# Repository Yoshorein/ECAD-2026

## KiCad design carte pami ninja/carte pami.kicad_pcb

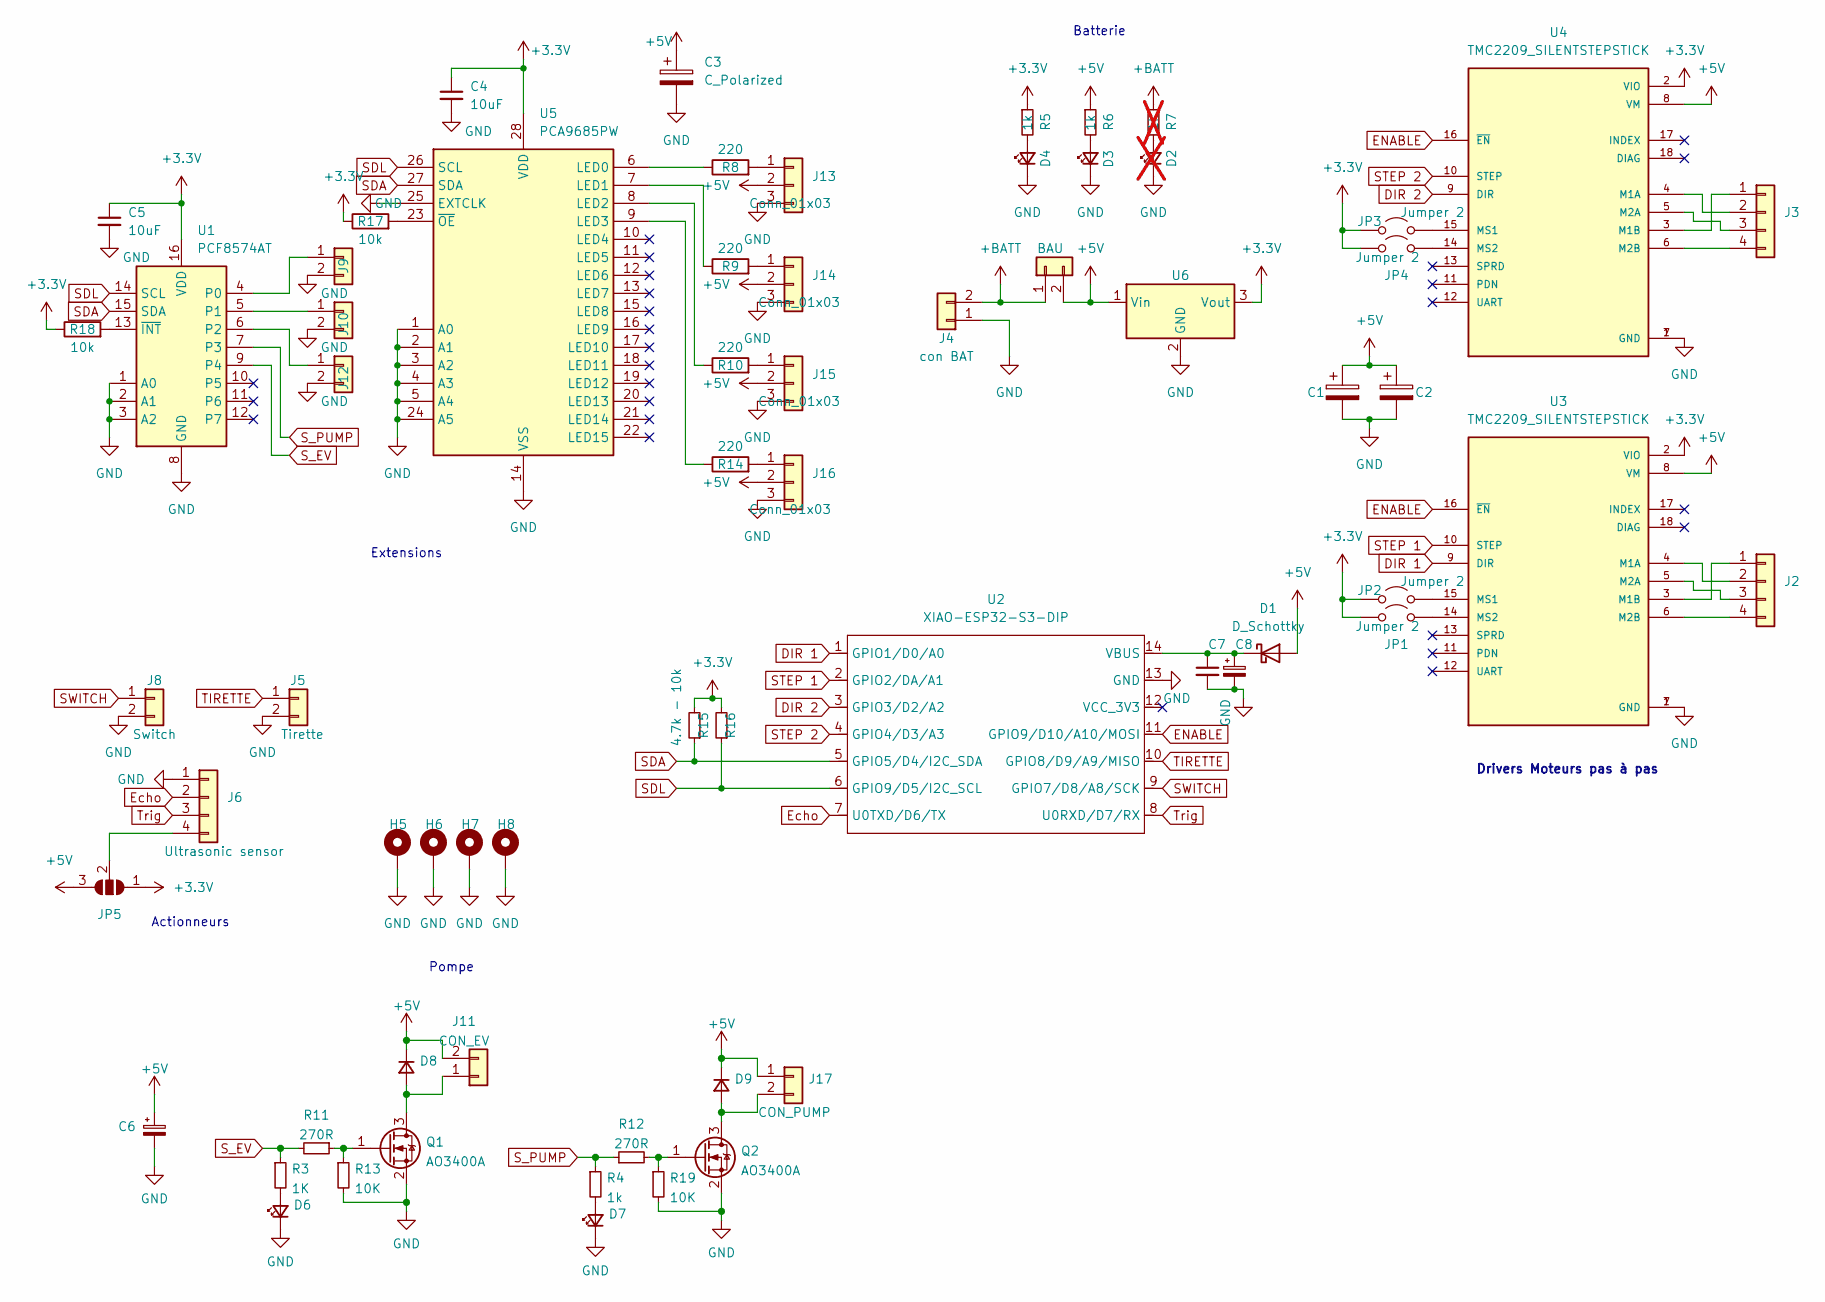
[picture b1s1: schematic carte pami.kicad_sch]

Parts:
C1, C2: C_Polarized; CP_Radial_D8.0mm_P3.80mm
C3: C_Polarized; CP_Radial_D8.0mm_P5.00mm
C4, C5: 10uF; C_1206_3216Metric_Pad1.33x1.80mm_HandSolder
C6: C_Polarized_Small; CP_Radial_D8.0mm_P5.00mm
C7: C_Small; C_1206_3216Metric_Pad1.33x1.80mm_HandSolder
C8: C_Polarized_Small; CP_Elec_6.3x3.9
D1: D_Schottky; D_DO-41_SOD81_P10.16mm_Horizontal
D2: LED_Small; LED_1206_3216Metric_Pad1.42x1.75mm_HandSolder; not fitted
D3, D4, D6, D7: LED_Small; LED_1206_3216Metric_Pad1.42x1.75mm_HandSolder
D8, D9: D_Small; D_SMA_Handsoldering
H5, H6, H7, H8: MountingHole_3.2mm_M3_Pad
J1: BAU; Molex_KK-254_AE-6410-02A_1x02_P2.54mm_Vertical
J2, J3: Conn_01x04; Molex_KK-254_AE-6410-04A_1x04_P2.54mm_Vertical
J4: con BAT; AMASS_XT60-F_1x02_P7.20mm_Vertical
J5: Tirette; Molex_KK-254_AE-6410-02A_1x02_P2.54mm_Vertical
J6: Ultrasonic sensor; Molex_KK-254_AE-6410-04A_1x04_P2.54mm_Vertical
J8: Switch; Molex_KK-254_AE-6410-02A_1x02_P2.54mm_Vertical
J9, J10, J12: Conn_01x02; Molex_KK-254_AE-6410-02A_1x02_P2.54mm_Vertical
J11: CON_EV; Molex_KK-254_AE-6410-02A_1x02_P2.54mm_Vertical
J13, J14, J15, J16: Conn_01x03; PinHeader_1x03_P2.54mm_Vertical
J17: CON_PUMP; Molex_KK-254_AE-6410-02A_1x02_P2.54mm_Vertical
JP1, JP2, JP3, JP4: Jumper 2; SolderJumper-2_P1.3mm_Open_RoundedPad1.0x1.5mm
JP5: SolderJumper_3_Open; SolderJumper-3_P1.3mm_Open_RoundedPad1.0x1.5mm_NumberLabels
Q1, Q2: AO3400A; SOT-23
R3: 1K; R_1206_3216Metric_Pad1.30x1.75mm_HandSolder
R4, R5, R6: 1k; R_1206_3216Metric_Pad1.30x1.75mm_HandSolder
R7: 1k; R_1206_3216Metric_Pad1.30x1.75mm_HandSolder; not fitted
R8, R9, R10, R14: 220; R_1206_3216Metric_Pad1.30x1.75mm_HandSolder
R11, R12: 270R; R_1206_3216Metric_Pad1.30x1.75mm_HandSolder
R13, R19: 10K; R_1206_3216Metric_Pad1.30x1.75mm_HandSolder
R15: 4.7k - 10k; R_1206_3216Metric_Pad1.30x1.75mm_HandSolder
R16: R_Small; R_1206_3216Metric_Pad1.30x1.75mm_HandSolder
R17, R18: 10k; R_1206_3216Metric_Pad1.30x1.75mm_HandSolder
U1: PCF8574AT; SOIC-16W_7.5x10.3mm_P1.27mm
U2: XIAO-ESP32-S3-DIP; XIAO-ESP32S3-DIP
U3, U4: TMC2209_SILENTSTEPSTICK; MODULE_TMC2209_SILENTSTEPSTICK; PARTREV 1.20
U5: PCA9685PW; TSSOP-28_4.4x9.7mm_P0.65mm
U6: TSR1-2433E; Converter_DCDC_TRACO_TSR1-xxxxE_THT

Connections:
+3.3V: C4.1, C5.1, JP1.1 (A), JP2.1 (A), JP3.1 (A), JP4.1 (A), JP5.1 (A), R5.1, R15.2, R16.2, R17.1, R18.1, U1.16 (VDD), U3.2 (VIO), U4.2 (VIO), U5.28 (VDD), U6.3 (Vout)
+5V: C1.1, C2.1, C3.1, C6.1, D1.2 (A), D8.1 (K), D9.1 (K), J1.2, J11.2, J13.2, J14.2, J15.2, J16.2, J17.1, JP5.3 (B), R6.1, U3.8 (VM), U4.8 (VM), U6.1 (Vin)
+BATT: J1.1, J4.2, R7.1
DIR 1: U2.1 (GPIO1/D0/A0), U3.9 (DIR)
DIR 2: U2.3 (GPIO3/D2/A2), U4.9 (DIR)
ENABLE: U2.11 (GPIO9/D10/A10/MOSI), U3.16 (~EN), U4.16 (~EN)
Echo: J6.2, U2.7 (U0TXD/D6/TX)
GND: C1.2, C2.2, C3.2, C4.2, C5.2, C6.2, C7.2, C8.2, D2.1 (K), D3.1 (K), D4.1 (K), D6.1 (K), D7.1 (K), H5.1, H6.1, H7.1, H8.1, J4.1, J5.2, J6.1, J8.2, J9.2, J10.2, J12.2, J13.3, J14.3, J15.3, J16.3, Q1.2 (S), Q2.2 (S), R13.2, R19.2, U1.1 (A0), U1.2 (A1), U1.3 (A2), U1.8 (GND), U2.13 (GND), U3.1 (GND), U3.7 (GND), U4.1 (GND), U4.7 (GND), U5.1 (A0), U5.2 (A1), U5.3 (A2), U5.4 (A3), U5.5 (A4), U5.14 (VSS), U5.24 (A5), U5.25 (EXTCLK), U6.2 (GND)
unnamed: C7.1, C8.1, D1.1 (K), U2.14 (VBUS)
unnamed: D2.2 (A), R7.2
unnamed: D3.2 (A), R6.2
unnamed: D4.2 (A), R5.2
unnamed: D6.2 (A), R3.2
unnamed: D7.2 (A), R4.2
unnamed: D8.2 (A), J11.1, Q1.3 (D)
unnamed: D9.2 (A), J17.2, Q2.3 (D)
unnamed: J2.1, U3.3 (M1B)
unnamed: J2.2, U3.4 (M1A)
unnamed: J2.3, U3.5 (M2A)
unnamed: J2.4, U3.6 (M2B)
unnamed: J3.1, U4.3 (M1B)
unnamed: J3.2, U4.4 (M1A)
unnamed: J3.3, U4.5 (M2A)
unnamed: J3.4, U4.6 (M2B)
unnamed: J6.4, JP5.2 (C)
unnamed: J9.1, U1.4 (P0)
unnamed: J10.1, U1.5 (P1)
unnamed: J12.1, U1.6 (P2)
unnamed: J13.1, R8.2
unnamed: J14.1, R9.2
unnamed: J15.1, R10.2
unnamed: J16.1, R14.2
unnamed: JP1.2 (B), U3.14 (MS2)
unnamed: JP2.2 (B), U3.15 (MS1)
unnamed: JP3.2 (B), U4.15 (MS1)
unnamed: JP4.2 (B), U4.14 (MS2)
unnamed: Q1.1 (G), R11.1, R13.1
unnamed: Q2.1 (G), R12.2, R19.1
unnamed: R18.2, U1.13 (~INT)
unnamed: R8.1, U5.6 (LED0)
unnamed: R9.1, U5.7 (LED1)
unnamed: R10.1, U5.8 (LED2)
unnamed: R14.1, U5.9 (LED3)
unnamed: R17.2, U5.23 (~OE)
SDA: R15.1, U1.15 (SDA), U2.5 (GPIO5/D4/I2C_SDA), U5.27 (SDA)
SDL: R16.1, U1.14 (SCL), U2.6 (GPIO9/D5/I2C_SCL), U5.26 (SCL)
STEP 1: U2.2 (GPIO2/DA/A1), U3.10 (STEP)
STEP 2: U2.4 (GPIO4/D3/A3), U4.10 (STEP)
SWITCH: J8.1, U2.9 (GPIO7/D8/A8/SCK)
S_EV: R3.1, R11.2, U1.9 (P4)
S_PUMP: R4.1, R12.1, U1.7 (P3)
TIRETTE: J5.1, U2.10 (GPIO8/D9/A9/MISO)
Trig: J6.3, U2.8 (U0RXD/D7/RX)

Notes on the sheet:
Batterie
Pompe
Actionneurs
Drivers Moteurs pas à pas
Extensions

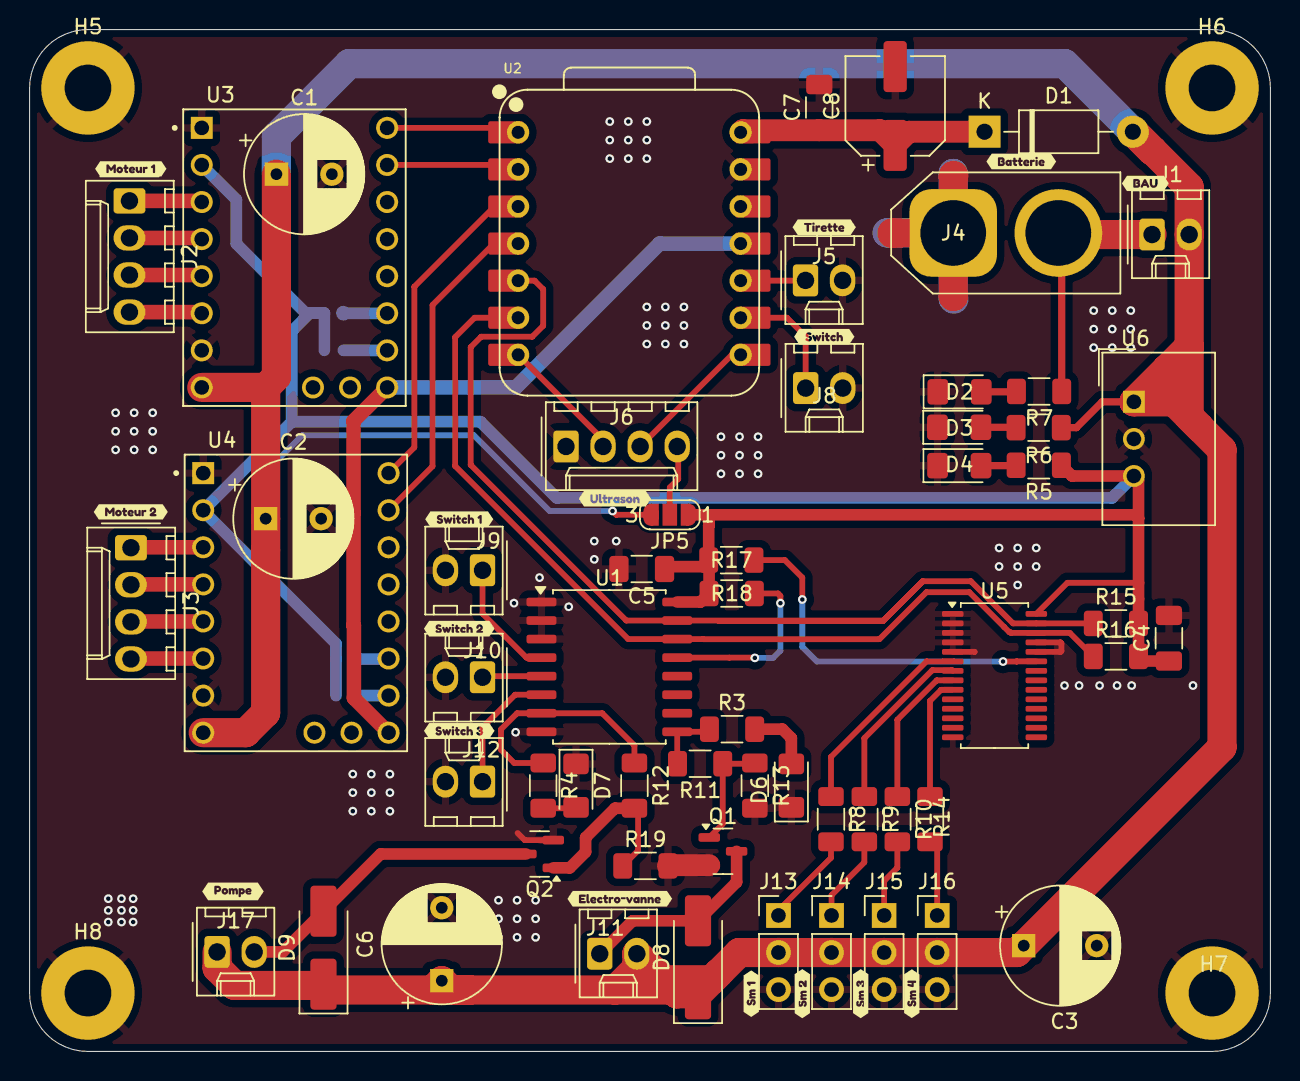
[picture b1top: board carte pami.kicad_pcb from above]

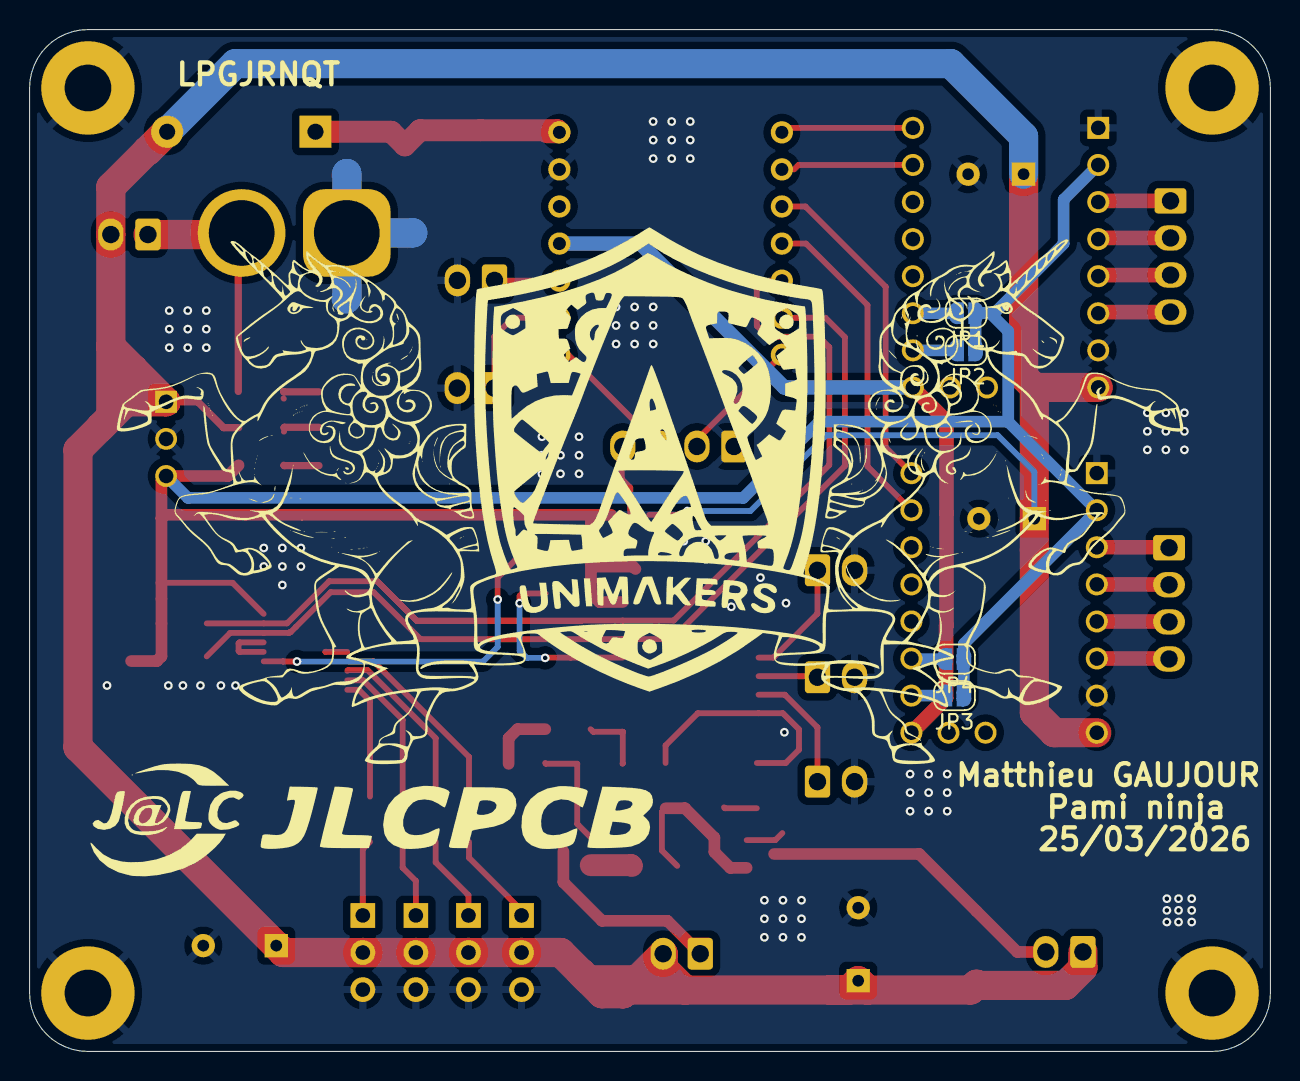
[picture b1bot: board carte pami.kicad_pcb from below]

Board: 2 copper layers, 85.0 x 70.0 mm, 82 parts (4 on the bottom side), 53 nets.

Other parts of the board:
kibuzzard-69BD4C51: G***; kibuzzard-69BD4C51
kibuzzard-69BD4C98: G***; kibuzzard-69BD4C98
kibuzzard-69BD4CAE: G***; kibuzzard-69BD4CAE
kibuzzard-69BD4CC4: G***; kibuzzard-69BD4CC4
kibuzzard-69BD4CEF: G***; kibuzzard-69BD4CEF
kibuzzard-69BD4D3C: G***; kibuzzard-69BD4D3C
kibuzzard-69BD4D5C: G***; kibuzzard-69BD4D5C
kibuzzard-69BD4D83: G***; kibuzzard-69BD4D83
kibuzzard-69BD4D93: G***; kibuzzard-69BD4D93
kibuzzard-69BD4EA4: G***; kibuzzard-69BD4EA4
kibuzzard-69BD4EB4: G***; kibuzzard-69BD4EB4
kibuzzard-69BD4EFE: G***; kibuzzard-69BD4EFE
kibuzzard-69BD4FA7: G***; kibuzzard-69BD4FA7
kibuzzard-69BD4FC7: G***; kibuzzard-69BD4FC7
kibuzzard-69BD4FD6: G***; kibuzzard-69BD4FD6
kibuzzard-69BD4FE1: G***; kibuzzard-69BD4FE1

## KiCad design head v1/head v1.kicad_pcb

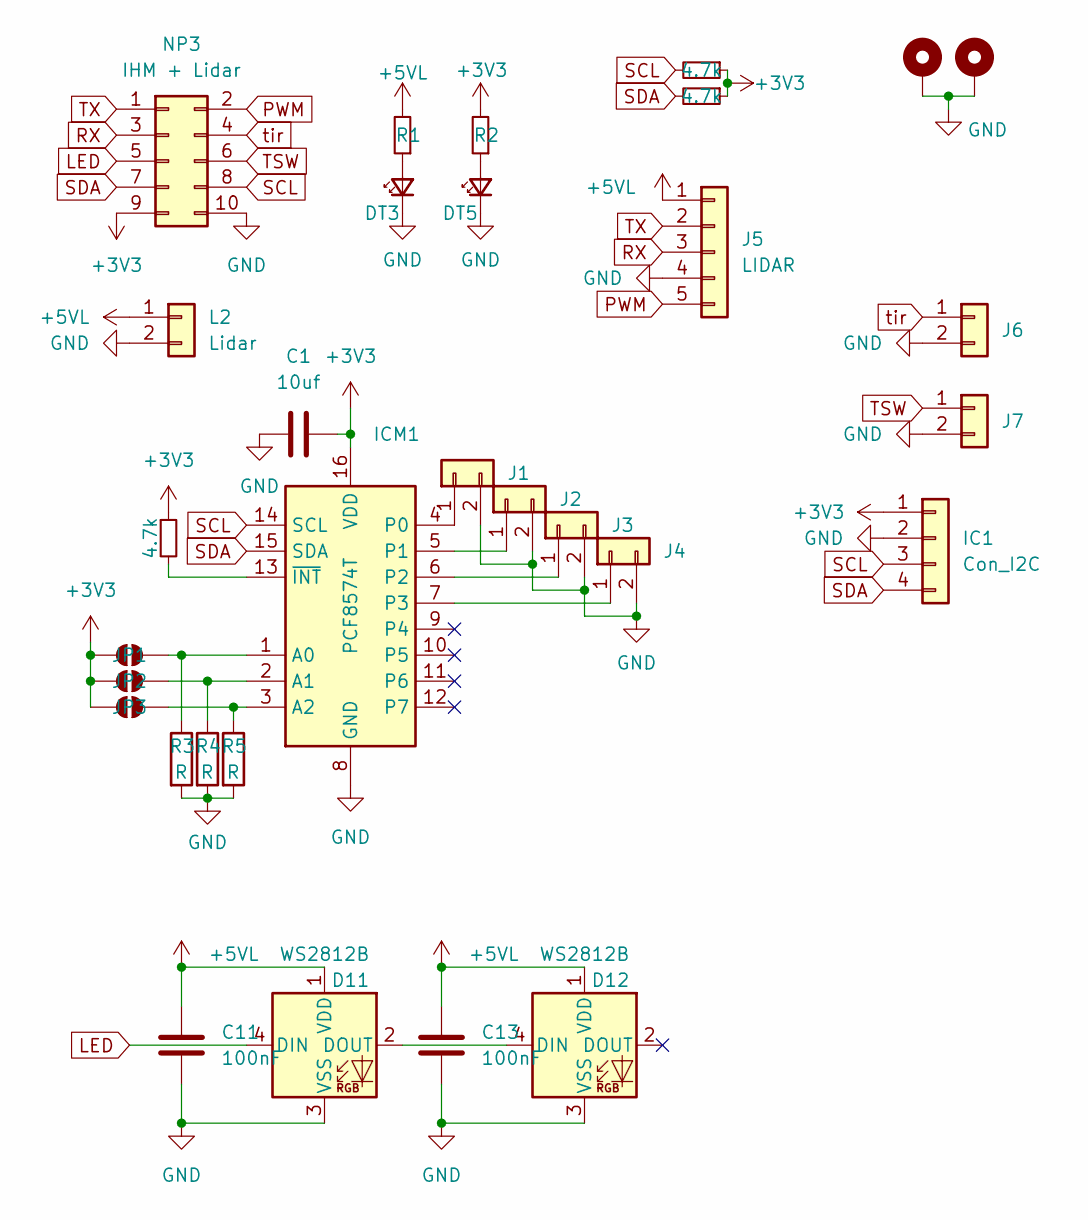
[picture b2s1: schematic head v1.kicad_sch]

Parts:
C1: 10uf; C_1206_3216Metric_Pad1.33x1.80mm_HandSolder
C11, C13: 100nF; C_1206_3216Metric
D11, D12: WS2812B; LED_WS2812B_PLCC4_5.0x5.0mm_P3.2mm
DT3, DT5: LED_Small; LED_1206_3216Metric_Pad1.42x1.75mm_HandSolder
H1, H2: M3; MountingHole_3.2mm_M3_Pad_Via
IC1: Con_I2C; Molex_KK-254_AE-6410-04A_1x04_P2.54mm_Vertical
ICM1: PCF8574T; SOIC-16W_7.5x10.3mm_P1.27mm
J1, J2, J3, J4, J6, J7: Conn_01x02; Molex_KK-254_AE-6410-02A_1x02_P2.54mm_Vertical
J5: LIDAR; JST_XH_B5B-XH-A_1x05_P2.50mm_Vertical
JP1, JP2, JP3: SolderJumper_2_Open; SolderJumper-2_P1.3mm_Open_RoundedPad1.0x1.5mm
L2: Lidar; Molex_KK-254_AE-6410-02A_1x02_P2.54mm_Vertical
NP3: IHM + Lidar; IDC-Header_2x05_P2.54mm_Vertical
R1, R2: R_Small; R_1206_3216Metric_Pad1.30x1.75mm_HandSolder
R3, R4, R5: R; R_1206_3216Metric_Pad1.30x1.75mm_HandSolder
R6, R7, R8: 4.7k; R_1206_3216Metric_Pad1.30x1.75mm_HandSolder

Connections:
+3V3: C1.1, IC1.1, ICM1.16 (VDD), JP1.1 (A), JP2.1 (A), JP3.1 (A), NP3.9, R2.2, R6.1, R7.1, R8.1; also elsewhere on the board
+5VL: C11.1, C13.1, D11.1 (VDD), D12.1 (VDD), J5.1, L2.1, R1.2
GND: C1.2, C11.2, C13.2, D11.3 (VSS), D12.3 (VSS), DT3.1 (K), DT5.1 (K), H1.1, H2.1, IC1.2, ICM1.8 (GND), J1.2, J2.2, J3.2, J4.2, J5.4, J6.2, J7.2, L2.2, NP3.10, R3.2, R4.2, R5.2
LED: D11.4 (DIN), NP3.5
unnamed: D11.2 (DOUT), D12.4 (DIN)
unnamed: DT3.2 (A), R1.1
unnamed: DT5.2 (A), R2.1
unnamed: ICM1.1 (A0), JP1.2 (B), R3.1
unnamed: ICM1.2 (A1), JP2.2 (B), R4.1
unnamed: ICM1.3 (A2), JP3.2 (B), R5.1
unnamed: ICM1.4 (P0), J1.1
unnamed: ICM1.5 (P1), J2.1
unnamed: ICM1.6 (P2), J3.1
unnamed: ICM1.7 (P3), J4.1
unnamed: ICM1.13 (~INT), R6.2
PWM: J5.5, NP3.2
RX: J5.3, NP3.3; also elsewhere on the board
SCL: IC1.3, ICM1.14 (SCL), NP3.8, R7.2
SDA: IC1.4, ICM1.15 (SDA), NP3.7, R8.2
TSW: J7.1, NP3.6
TX: J5.2, NP3.1; also elsewhere on the board
tir: J6.1, NP3.4

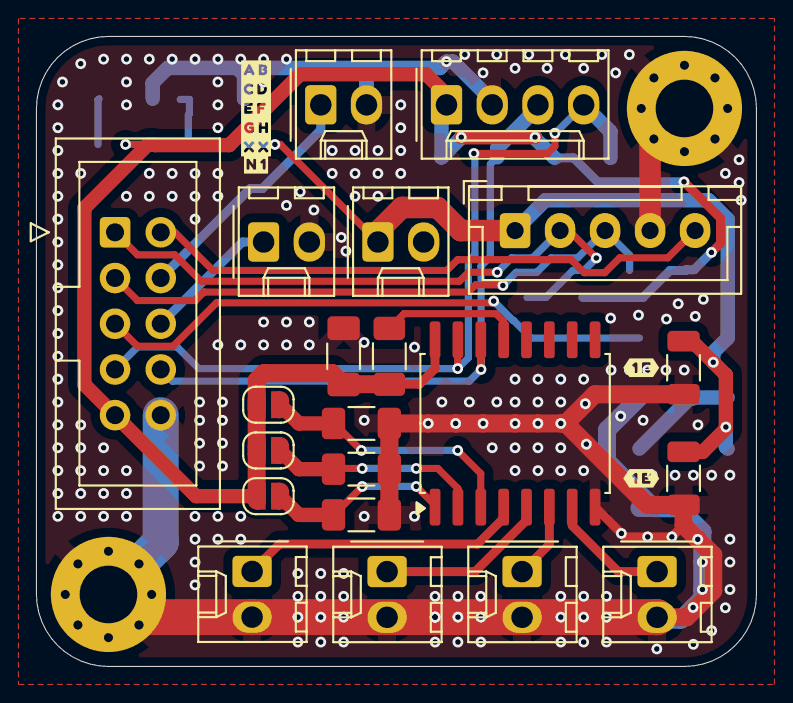
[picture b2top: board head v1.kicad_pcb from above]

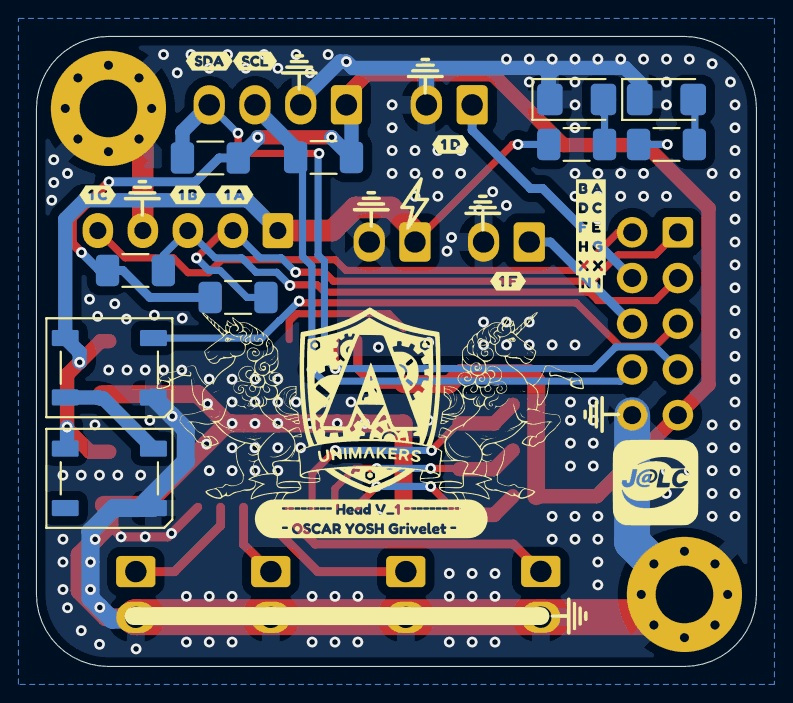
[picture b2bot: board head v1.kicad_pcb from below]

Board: 2 copper layers, 40.0 x 35.0 mm, 47 parts (20 on the bottom side), 22 nets.

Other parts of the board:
R9, R10: 4.7k; R_1206_3216Metric_Pad1.30x1.75mm_HandSolder
kibuzzard-69B7FFCA: G***; kibuzzard-69B7FFCA
kibuzzard-69B800EA, kibuzzard-69B800EA#2: G***; kibuzzard-69B800EA
kibuzzard-69BAE0CF, kibuzzard-69BAE0CF#2: G***; kibuzzard-69BAE0CF
kibuzzard-69BAE8DD: G***; kibuzzard-69BAE8DD
kibuzzard-69BAE75D: G***; kibuzzard-69BAE75D
kibuzzard-69BAE350: G***; kibuzzard-69BAE350
kibuzzard-69BAE766: G***; kibuzzard-69BAE766
kibuzzard-69BAED5C: G***; kibuzzard-69BAED5C
kibuzzard-69BAED6C: G***; kibuzzard-69BAED6C
kibuzzard-69BAED73: G***; kibuzzard-69BAED73
kibuzzard-69BAED80: G***; kibuzzard-69BAED80
kibuzzard-69C6521F: G***; kibuzzard-69C6521F

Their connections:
+3V3: R9.1, R10.1; also elsewhere on the board
RX: R10.2; also elsewhere on the board
TX: R9.2; also elsewhere on the board

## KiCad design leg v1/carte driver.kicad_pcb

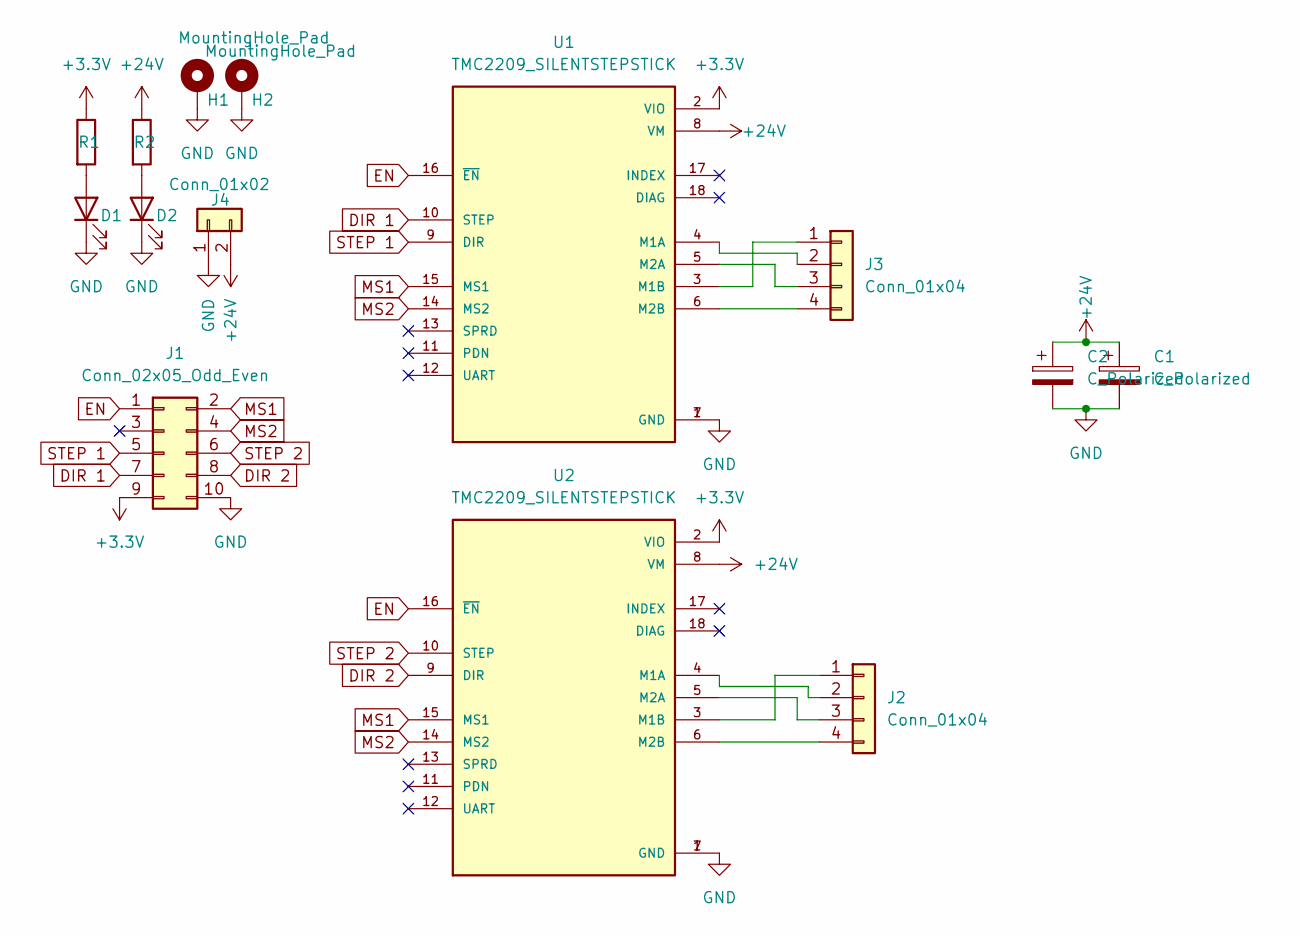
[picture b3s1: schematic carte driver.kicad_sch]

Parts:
C1, C2: C_Polarized; CP_Radial_D10.0mm_P5.00mm
D1, D2: LED; LED_1206_3216Metric_Pad1.42x1.75mm_HandSolder
H1, H2: MountingHole_Pad; MountingHole_3.2mm_M3_Pad_Via
J1: Conn_02x05_Odd_Even; IDC-Header_2x05_P2.54mm_Vertical
J2, J3: Conn_01x04; Molex_KK-254_AE-6410-04A_1x04_P2.54mm_Vertical
J4: Conn_01x02; AMASS_XT30U-M_1x02_P5.0mm_Vertical
R1, R2: R; R_1206_3216Metric_Pad1.30x1.75mm_HandSolder
U1, U2: TMC2209_SILENTSTEPSTICK; MODULE_TMC2209_SILENTSTEPSTICK; PARTREV 1.20

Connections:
+3.3V: J1.9, R1.1, U1.2 (VIO), U2.2 (VIO)
+24V: C1.1, C2.1, J4.2, R2.1, U1.8 (VM), U2.8 (VM)
DIR 1: J1.7, U1.10 (STEP)
DIR 2: J1.8, U2.9 (DIR)
EN: J1.1, U1.16 (~EN), U2.16 (~EN)
GND: C1.2, C2.2, D1.1 (K), D2.1 (K), H1.1, H2.1, J1.10, J4.1, U1.1 (GND), U1.7 (GND), U2.1 (GND), U2.7 (GND)
MS1: J1.2, U1.15 (MS1), U2.15 (MS1)
MS2: J1.4, U1.14 (MS2), U2.14 (MS2)
unnamed: D1.2 (A), R1.2
unnamed: D2.2 (A), R2.2
unnamed: J2.1, U2.3 (M1B)
unnamed: J2.2, U2.4 (M1A)
unnamed: J2.3, U2.5 (M2A)
unnamed: J2.4, U2.6 (M2B)
unnamed: J3.1, U1.3 (M1B)
unnamed: J3.2, U1.4 (M1A)
unnamed: J3.3, U1.5 (M2A)
unnamed: J3.4, U1.6 (M2B)
STEP 1: J1.5, U1.9 (DIR)
STEP 2: J1.6, U2.10 (STEP)

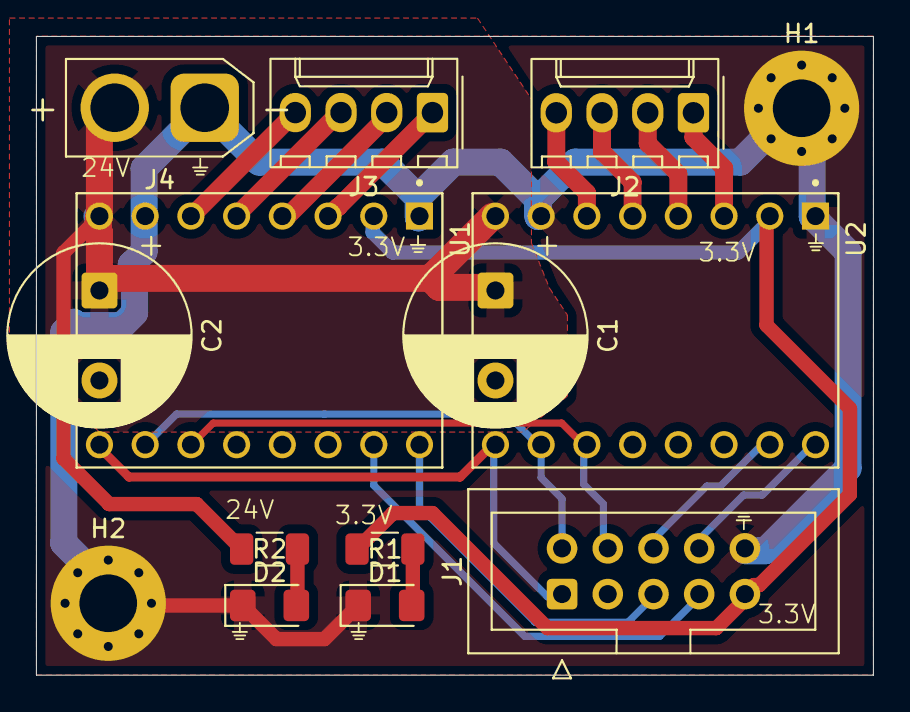
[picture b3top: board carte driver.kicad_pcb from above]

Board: 2 copper layers, 46.5 x 35.5 mm, 14 parts (0 on the bottom side), 20 nets.

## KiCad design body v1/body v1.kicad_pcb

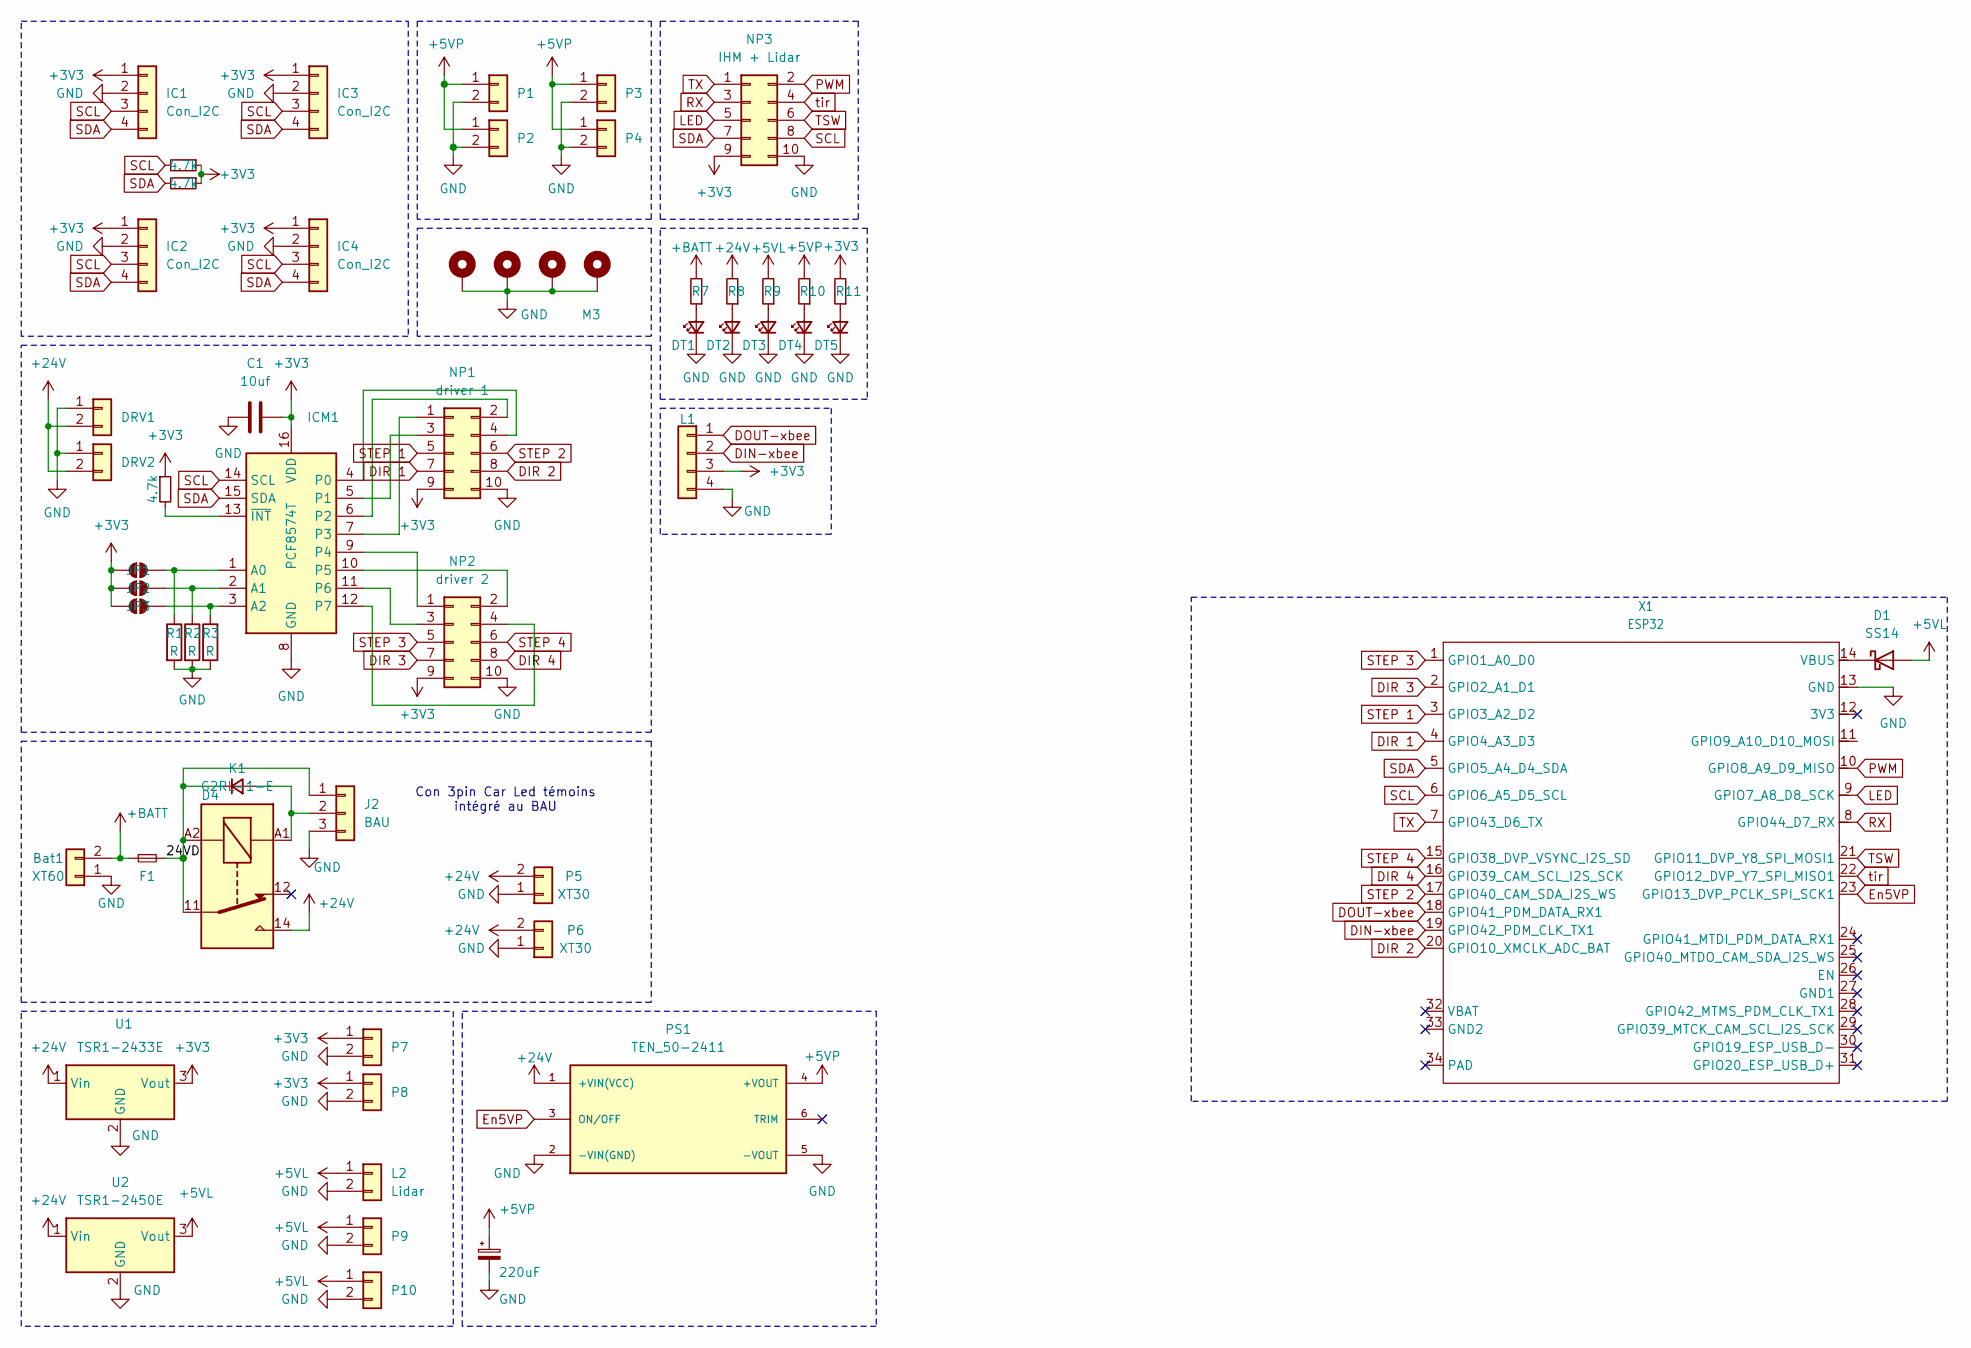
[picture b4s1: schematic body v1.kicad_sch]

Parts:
Bat1: XT60; AMASS_XT60-M_1x02_P7.20mm_Vertical
C1: 10uf; C_1206_3216Metric_Pad1.33x1.80mm_HandSolder
C6: 220uF; CP_Radial_D8.0mm_P3.80mm
D1: SS14; D_SMA
D4: D_Small; D_SMA_Handsoldering
DRV1, DRV2: Conn_01x02; AMASS_XT30U-M_1x02_P5.0mm_Vertical
DT1, DT2, DT3, DT4, DT5: LED_Small; LED_1206_3216Metric_Pad1.42x1.75mm_HandSolder
F1: Fuse_Small; Fuseholder_Blade_Mini_Keystone_3568
H1, H2, H3, H4: M3; MountingHole_3.2mm_M3_Pad_Via
IC1, IC2, IC3, IC4: Con_I2C; Molex_KK-254_AE-6410-04A_1x04_P2.54mm_Vertical
ICM1: PCF8574T; SOIC-16W_7.5x10.3mm_P1.27mm
J2: BAU; Molex_KK-254_AE-6410-03A_1x03_P2.54mm_Vertical
JP1, JP2, JP3: SolderJumper_2_Open; SolderJumper-2_P1.3mm_Open_RoundedPad1.0x1.5mm
K1: G2RL-1-E; Relay_SPDT_Omron_G2RL-1-E
L1: Conn_01x04; Molex_KK-254_AE-6410-04A_1x04_P2.54mm_Vertical
L2: Lidar; Molex_KK-254_AE-6410-02A_1x02_P2.54mm_Vertical
NP1: driver 1; IDC-Header_2x05_P2.54mm_Vertical
NP2: driver 2; IDC-Header_2x05_P2.54mm_Vertical
NP3: IHM + Lidar; IDC-Header_2x05_P2.54mm_Vertical
P1, P2, P3, P4: Conn_01x02; Molex_KK-254_AE-6410-02A_1x02_P2.54mm_Vertical
P5, P6: XT30; AMASS_XT30U-M_1x02_P5.0mm_Vertical
P7, P8, P9, P10: Molex_KK-254_AE-6410-02A_1x02_P2.54mm_Vertical
PS1: TEN_50-2411; CONV_TEN_50-2411; PARTREV February 3, 2021
R1, R2, R3: R; R_1206_3216Metric_Pad1.30x1.75mm_HandSolder
R4, R5, R6: 4.7k; R_1206_3216Metric_Pad1.30x1.75mm_HandSolder
R7, R8, R9, R10, R11: R_Small; R_1206_3216Metric_Pad1.30x1.75mm_HandSolder
U1: TSR1-2433E; Converter_DCDC_TRACO_TSR1-xxxxE_THT
U2: TSR1-2450E; Converter_DCDC_TRACO_TSR1-xxxxE_THT
X1: ESP32; xiao s3+

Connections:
+3V3: C1.1, IC1.1, IC2.1, IC3.1, IC4.1, ICM1.16 (VDD), JP1.1 (A), JP2.1 (A), JP3.1 (A), L1.3, NP1.9, NP2.9, NP3.9, P7.1, P8.1, R4.1, R5.1, R6.1, R11.2, U1.3 (Vout)
+5VL: D1.2 (A), L2.1, P9.1, P10.1, R9.2, U2.3 (Vout)
+5VP: C6.1, P1.1, P2.1, P3.1, P4.1, PS1.4 (+VOUT), R10.2
+24V: DRV1.2, DRV2.2, K1.14, P5.2, P6.2, PS1.1 (+VIN(VCC)), R8.2, U1.1 (Vin), U2.1 (Vin)
+BATT: Bat1.2, F1.1, R7.2
/24VD: D4.1 (K), F1.2, J2.1, K1.11, K1.A2
DIN-xbee: L1.2, X1.19 (GPIO42_PDM_CLK_TX1)
DIR 1: NP1.7, X1.4 (GPIO4_A3_D3)
DIR 2: NP1.8, X1.20 (GPIO10_XMCLK_ADC_BAT)
DIR 3: NP2.7, X1.2 (GPIO2_A1_D1)
DIR 4: NP2.8, X1.16 (GPIO39_CAM_SCL_I2S_SCK)
DOUT-xbee: L1.1, X1.18 (GPIO41_PDM_DATA_RX1)
En5VP: PS1.3 (ON/OFF), X1.23 (GPIO13_DVP_PCLK_SPI_SCK1)
GND: Bat1.1, C1.2, C6.2, DRV1.1, DRV2.1, DT1.1 (K), DT2.1 (K), DT3.1 (K), DT4.1 (K), DT5.1 (K), H1.1, H2.1, H3.1, H4.1, IC1.2, IC2.2, IC3.2, IC4.2, ICM1.8 (GND), J2.3, L1.4, L2.2, NP1.10, NP2.10, NP3.10, P1.2, P2.2, P3.2, P4.2, P5.1, P6.1, P7.2, P8.2, P9.2, P10.2, PS1.2 (-VIN(GND)), PS1.5 (-VOUT), R1.2, R2.2, R3.2, U1.2 (GND), U2.2 (GND), X1.13 (GND)
LED: NP3.5, X1.9 (GPIO7_A8_D8_SCK)
unnamed: D1.1 (K), X1.14 (VBUS)
unnamed: D4.2 (A), J2.2, K1.A1
unnamed: DT1.2 (A), R7.1
unnamed: DT2.2 (A), R8.1
unnamed: DT3.2 (A), R9.1
unnamed: DT4.2 (A), R10.1
unnamed: DT5.2 (A), R11.1
unnamed: ICM1.1 (A0), JP1.2 (B), R1.1
unnamed: ICM1.2 (A1), JP2.2 (B), R2.1
unnamed: ICM1.3 (A2), JP3.2 (B), R3.1
unnamed: ICM1.4 (P0), NP1.4
unnamed: ICM1.5 (P1), NP1.3
unnamed: ICM1.6 (P2), NP1.2
unnamed: ICM1.7 (P3), NP1.1
unnamed: ICM1.9 (P4), NP2.1
unnamed: ICM1.10 (P5), NP2.2
unnamed: ICM1.11 (P6), NP2.3
unnamed: ICM1.12 (P7), NP2.4
unnamed: ICM1.13 (~INT), R4.2
PWM: NP3.2, X1.10 (GPIO8_A9_D9_MISO)
RX: NP3.3, X1.8 (GPIO44_D7_RX)
SCL: IC1.3, IC2.3, IC3.3, IC4.3, ICM1.14 (SCL), NP3.8, R5.2, X1.6 (GPIO6_A5_D5_SCL)
SDA: IC1.4, IC2.4, IC3.4, IC4.4, ICM1.15 (SDA), NP3.7, R6.2, X1.5 (GPIO5_A4_D4_SDA)
STEP 1: NP1.5, X1.3 (GPIO3_A2_D2)
STEP 2: NP1.6, X1.17 (GPIO40_CAM_SDA_I2S_WS)
STEP 3: NP2.5, X1.1 (GPIO1_A0_D0)
STEP 4: NP2.6, X1.15 (GPIO38_DVP_VSYNC_I2S_SD)
TSW: NP3.6, X1.21 (GPIO11_DVP_Y8_SPI_MOSI1)
TX: NP3.1, X1.7 (GPIO43_D6_TX)
tir: NP3.4, X1.22 (GPIO12_DVP_Y7_SPI_MISO1)

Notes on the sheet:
Con 3pin Car Led témoins intégré au BAU
